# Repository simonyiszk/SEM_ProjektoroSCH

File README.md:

# RS232 Remote control
This project is created for wall mounted remote control of a projector's power settings and input selection.

## Protocol basics:
RS232 in a nutshell: https://docs.google.com/document/d/1p7Dz5NA0ECTMzfMRH148HRk15ERgRvAex5ETr_D8jeQ/edit?usp=sharing

## Project workflow:
- [x] Schematic design
- [ ] Firmwware developent
- [ ] Case design
- [ ] Protoype testing

## Project is made possible by Schönherz Elektronikai Műhely (SEM)

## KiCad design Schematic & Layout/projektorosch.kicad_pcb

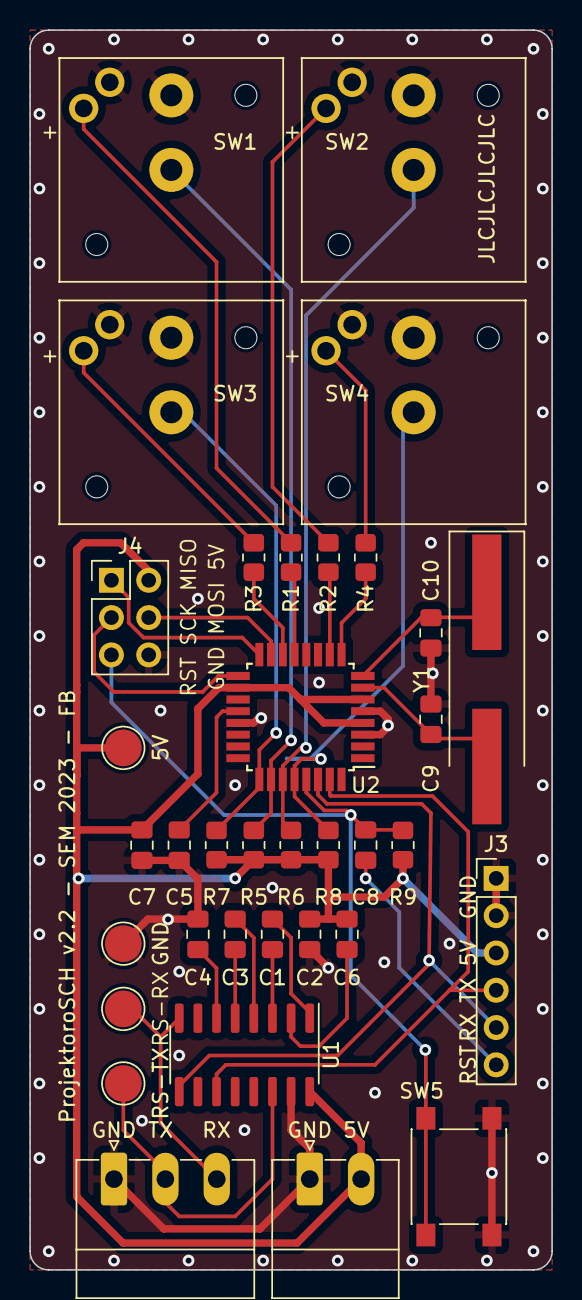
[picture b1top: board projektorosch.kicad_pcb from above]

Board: 2 copper layers, 35.6 x 84.5 mm, 35 parts (0 on the bottom side), 32 nets.

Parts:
5V: 5V; TestPoint_Pad_D2.5mm
C1, C2, C3, C4, C5, C6, C7, C8: 0.1uF; C_0805_2012Metric_Pad1.18x1.45mm_HandSolder
C9, C10: 22pF; C_0805_2012Metric_Pad1.18x1.45mm_HandSolder
GND: GND; TestPoint_Pad_D2.5mm
J1: Power; PhoenixContact_MC_1,5_2-G-3.5_1x02_P3.50mm_Horizontal
J2: RS232; PhoenixContact_MC_1,5_3-G-3.5_1x03_P3.50mm_Horizontal
J3: Programmer; PinHeader_1x06_P2.54mm_Vertical
J4: ISP; PinHeader_2x03_P2.54mm_Vertical
R1, R2, R3, R4: 150; R_0805_2012Metric_Pad1.20x1.40mm_HandSolder
R5, R6, R7, R8, R9: 10k; R_0805_2012Metric_Pad1.20x1.40mm_HandSolder
RS-RX: 232-RX; TestPoint_Pad_D2.5mm
RS-TX: 232-TX; TestPoint_Pad_D2.5mm
SW1, SW2, SW3, SW4: SW_SPST; Marquardt 64250101
SW5: Reset; SW_Push_1P1T_NO_6x6mm_H9.5mm
U1: MAX232; SOP-16_3.9x9.9mm_P1.27mm
U2: ATmega328P-A; TQFP-32_7x7mm_P0.8mm
Y1: 16MHz; Crystal_SMD_HC49-SD_HandSoldering

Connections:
232-RX: J2.3, RS-RX.1, U1.8 (R2IN)
232-TX: J2.2, RS-TX.1, U1.14 (T1OUT)
+5V: 5V.1, C2.1, C6.2, C7.2, J1.2, J3.3, J4.2, R5.2, R6.2, R7.2, R8.2, R9.2, U1.16 (VCC), U2.4 (VCC), U2.6 (VCC), U2.18 (AVCC)
BTN-1: R5.1, SW1.2 (B), U2.26 (PC3)
BTN-2: R6.1, SW2.2 (B), U2.27 (PC4)
BTN-3: R7.1, SW3.2 (B), U2.25 (PC2)
BTN-4: R8.1, SW4.2 (B), U2.28 (PC5)
GND: C2.2, C4.1, C5.1, C7.1, C9.1, C10.1, GND.1, J1.1, J2.1, J3.1, J3.2, J4.6, SW1.1 (A), SW1.4 (K), SW2.1 (A), SW2.4 (K), SW3.1 (A), SW3.4 (K), SW4.1 (A), SW4.4 (K), SW5.1 (A), U1.15 (GND), U2.3 (GND), U2.5 (GND), U2.21 (GND)
MCU-RX: J3.5, U1.9 (R2OUT), U2.30 (PD0)
MCU-TX: J3.4, U1.11 (T1IN), U2.31 (PD1)
MISO: J4.1, U2.16 (PB4)
MOSI: J4.4, U2.15 (PB3)
unnamed: R1.1, SW1.3 (A)
unnamed: R2.1, SW2.3 (A)
unnamed: R3.1, SW3.3 (A)
unnamed: R4.1, SW4.3 (A)
unnamed: C1.1, U1.1 (C1+)
unnamed: C1.2, U1.3 (C1-)
unnamed: C3.1, U1.4 (C2+)
unnamed: C3.2, U1.5 (C2-)
unnamed: C6.1, U1.2 (VS+)
unnamed: C4.2, U1.6 (VS-)
unnamed: C5.2, U2.20 (AREF)
unnamed: C9.2, U2.7 (XTAL1/PB6), Y1.2
unnamed: C10.2, U2.8 (XTAL2/PB7), Y1.1
PROG-DTR: C8.2, J3.6
PWM-1: R1.2, U2.13 (PB1)
PWM-2: R2.2, U2.10 (PD6)
PWM-3: R3.2, U2.14 (PB2)
PWM-4: R4.2, U2.9 (PD5)
RST: C8.1, J4.5, R9.1, SW5.2 (B), U2.29 (~RESET/PC6)
SCK: J4.3, U2.17 (PB5)

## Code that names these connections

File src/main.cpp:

#include <Arduino.h>
#include "config.h"

enum FunctionTypes
{
    powerOn = PIN_PC3,
    powerOff = PIN_PC4,
    source = PIN_PC2,
    source2 = PIN_PC5
};

int functionPins[] = {PIN_PC3, PIN_PC4, PIN_PC2, PIN_PC5}; // gombok
int ledPins[] = {PIN_PB1, PIN_PD6, PIN_PB2, PIN_PD5};      // ledek

FunctionTypes readInput(bool& lastStatus)
{
    for (int i = 0; i < 4; i++)
    {
        if (!digitalRead(functionPins[i])) // 0-ban aktívak a bemenetek!
        {
            delay(50); //Pergésmentesítés
            if(!digitalRead(functionPins[i])) {
                if (!lastStatus)
                {
                    lastStatus = true;
                    return FunctionTypes(functionPins[i]); // Első gomnyomás
                }
                else
                    return FunctionTypes(0); // Ha volt gombnyomás de már a sokadik
            }
        }
    }
    lastStatus = false;
    return FunctionTypes(0); // Nincs gombnyomás
}

void setupFunctionPins()
{
    for (int i = 0; i < 4; i++)
    {
        pinMode(functionPins[i], INPUT);
    }
}

void setupLedPins()
{
    for (int i = 0; i < 4; i++)
    {
        pinMode(ledPins[i], OUTPUT);
        digitalWrite(ledPins[i], LOW); // Minden led lekapcsolása
    }
}

void setup()
{
    Serial.begin(BAUDRATE);
    delay(50);
    setupFunctionPins();
    setupLedPins();
}

Projector p1(acer);

bool lastStatus = false;
void loop()
{
    switch (readInput(lastStatus))
    {
    case powerOn:
        //digitalWrite(PIN_PD5, HIGH); ide lehet írni led vezérléseket, ki kell találni, hogy mi legyen
        p1.printHexToSerial(p1.turnOnCodes);
        break;

    case powerOff:
        p1.printHexToSerial(p1.turnOffCodes);
        //digitalWrite(PIN_PD5, LOW);
        break;

    case source:
        p1.printHexToSerial(p1.sourceCodes);
        break;

    case source2:
        p1.printHexToSerial(p1.source2Codes);
        break;

    default:
        break;
    }
}

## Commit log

2021-12-07 README.md created
2021-12-07 LICENSE created
2021-12-07 Folder structure added
2021-12-11 Sample code added for sparkfun pro micro, Gitignore added for vscode
2021-12-16 Datastructure, external config file and basic debug functions added.
2022-02-22 Schematic for arduino basic operation and few connectros added
2022-03-01 add buttons, and the connections of max232
2022-03-07 Improvements, add overvoltage and overcurrent protection
2022-03-15 assign footprints
2022-03-23 design pcb - first try
2022-03-25 redesign layout for attiny3216
2022-03-25 attiny214
2022-03-25 attinty3216-remeljuk-final
2022-03-25 attiny214 - the right files
2022-03-29 fixes
2022-03-29 final
2022-09-08 normal buttons
2024-03-05 SEM ProjektoroSCH Revision 2
2024-03-06 Remove PCB fixer spikes from Doboz
2024-03-20 Új source kódok a vezérlőhöz
    Jelenleg, még a pinMode beállításának kell utánajárni, és a szoftver nem lett érdemlegesen letesztelve.
2024-04-03 Add serial command tester script
2024-04-07 Doboz v5
2024-04-07 Doboz v6: -Szélesség növelve -Felfogató lenti hengerek megnagyobbítva -Lekerekítések éleknél, sarkoknál -Nyákot odaszorító dolgok
2024-04-08 Doboz v6 fix
2024-04-10 Tesztelésre elvileg kész src fájlok
    Hibát kell keresni, hogy mi miatt nem működik semmilyen soros kommunikáció normálisan
2024-04-23 Doboz v6.2 -félautomata méretezés javítások -méret finomhangolások próbanyomtatás alapján
2024-06-02 Majdnem teljesen kész kód
    Acer és Benq projektorokra készek a műveletek, LED vezérlést kell kitalálni, hogy hogyan legyen, és azt onnantól pár sor belekódolni.
    NEC projektor azóta sem bírtam működésre, de először legyen kész és felszerelve az acer és a benq.
